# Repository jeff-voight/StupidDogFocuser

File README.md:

# StupidDogFocuser

## Open-source electronic telescope focuser

The StupidDogFocuser is a work-in-progress prototype electronic focuser. It shall eventually comply with ASCOM and INDI and should operate on Linux, Windows, or Mac.

## Goals

The goal of this project is to develop an electronic focuser that is compact, free of airwires, capable of being mounted to a variety of telescope focusers controllable via a PCB-mounted knob, serial commands, and INDI and ASCOM software. It should be inexpensive, easy to build at home, and only use components that are easy to acquire.

Ultimately, I want somebody to be able to have a neat, compact focuser for under $100 and their time and solder.

## Size and Shape

The PCB is a shield for an Arduino UNO R3. I hope to be able to etch and solder the board at home, but it should also be designed in such a way that one could order a commercially manufactured board. The KiCad design files will be included. The initial builds will be geared toward a commercial board house.

The board is approximately the same shape as the UNO. It receives the 12V power directly from the Arduino. That means that you need to plug the Arduino into a 12V 1A power supply. These are available where you bought the Arduino. We could get more torque and speed if we went with a higher voltage, but we don't really need more torque or speed.

On one end is an optional temperature/humidity sensor. During assembly, the legs of the package need to be bent so that the sensor can be layed flat extended out in space beyond the board. This, hopefully, keeps the sensor far enough away from the driver that it isn't affected and it provides a way to extend the sensor out of an enclosure to give it access to the outdoor air.

The board features a mounted rotary encoder for handheld use. In fact, if one were so inclined, one wouldn't necessarily need to enclose this focuser. One could very easily just put the hat on the arduino, wire up the motor, plug it into 12V, and hold the thing bare and be up and running without an enclosure.

Heck, you could hot glue the whole thing right on your observatory wall or telescope mount and be fine. Maybe clean the spiders out from time to time. I mean, don't let it rain on it, but you weren't going to let it rain on your telescopes, right? 

The encoder has 30 detents, but something I didn't realize at first was that the encoder counts two steps per detent. At first I fretted about this, but at 5400 steps per rotation on a 27:1 geared stepper running at half-stepping (for torque and performance), two steps per detent seemed like an acceptable trade-off. If you're running a 200 step stepper, you *should* still be okay on a refractor or reflector. I can't say for an SCT.

## Enclosure
Included is a 3d-printable set of STL files that worked for me. It even has a knob.

I printed mine in glow-in-the-dark. It has never helped.

I hope to find a more professional enclosure, but I'm not actively looking.

Along with the enclosure, I haven't included the panel-mount electrical connector because I haven't found a 6 pin connector that I like.

I'm currently using a 4-pin aircraft something something. If you have a 6-pin (2 pins for the limit switch) connector that you love and you 
can find it on digikey, feel free to fork the code and submit a pull request.

## Assembly
The PCB is designed to use the same resistors and the same capacitors throughout. You can't go wrong. Just solder the resistors in wherever you see a resistor footprint and the same for the capacitors.

The DHT11 or DHT22 needs to be layed flat if you want it to stick out of an enclosure. This bend needs to be done before soldering.

The motor screw terminals should probably face in the same direction as the wires are going to go. There should be enough space to flip it around.

The Schmidtt Trigger footprint includes a dot and a little slanty line to indicate the dotted end of the chip. Make sure you get the orientation correct.

Likewise, the DRV8825 footprint includes a white rectangle on the same end that the chip of the DRV8825 daughterboard has. Make sure those line up, too.

The DRV8825 *ABSOLUTELY* needs the heatsink that comes with it. Make sure you put that thing on. It didn't take me but a few minutes to roast one of mine during development because I was being lazy.

The DRV8825 *ABSOLUTELY* needs to be adjusted before plugging in your first stepper. The steppers that I've been getting have been running best at about .8A per coil. But, the motor gets HOT.

### DIY disclaimer
I'm not opposed to through-hole parts, but I personally find drilling boards to be the most difficult part of home manufacture of PCB, I'd rather keep the drill-file to a minimum. Consider that you're going to be drilling all of the Arduino header pins and all of the component pins. It's probably safest to order the boards from a board house. However, if you only drill out the holes you need, you can save a whole bunch of the arduino pin holes. You technically only need one ground pin. Make sure you carry the 12V and 5V pins through.

The KiCad PCBs will be done for _my_ convenience for now. That means tiny traces and silkscreen that I wouldn't dare do at home and drill holes galor and if I feel like throwing in a via collection that carries signals and looks like a moose, that's my prerogative.

I mean, I probably won't, but just in case I do.

## Calibration and limit switches

Another goal is a limit switch and a reset routine. Upon hard reset (if there is such a thing), on power-up, it would store it's current position, rack the focuser IN until it touched the limit switch, reset everything such the limit switch is the low limit and the original position gets restored to it's whatever position it was before. I've included the pins for the limit switch, but I haven't yet worked out a homing routine. When it happens, you'll probably need to build a focuser for each telescope you want to drive because the results of the homing and length of focus will get stored in EEPROM.

One way or another, I feel like I need some type of security such that my cameras never fall to the floor or I end up stripping a gear on the focuser.

That said, it hasn't been a problem _yet_.

## Power-Off Conditions

For the time being, all is lost on reset/power-off. We start the focuser in the 20,000s. That should be enough to give a couple of inward turns of a knob.

A limit switch would solve this.

# As it is

As it is, we communicate at 115,200 baud. We depend on AccelStepper and a high performance encoder library, so I don't want to slow either of those down with slow serial performance. Our signal is only going a few feet, and unless you've got outrageous amounts of noise, 115,200 will be fine.

# Commands

Serial commands are as follows:

| Command | Description | Response        | Defaults | Comments |
| ---     | ---         | ---             | ---      | --- |
| \<HA>	  | Halt        | HA!             | N/A      | as quickly as possible |
| \<GE> 	  | Is enabled? | [T\|F]!          | True     | Motor Driver |
| \<GR>     | Is reversed?| [T\|F]!          | False    | Motor direction |
| \<GM>     | Microsteps  | [1-32]!         | _(1/)_1  | Denominator (not yet functional) | 
| \<GH>     | High limit  | MAXINT! | 108000    | Distance from initial |
| \<GL>     | Low limit   | [0! | 0  | 32 bit int |
| \<GS>     | Speed       | [0-255]!      | 255     | Stepper motor dependent |
| \<GT>     | Temperature | %f.2!             | N/A      | DHT11/22 precision  |
| \<GP>     | Position    | 0-MAXINT! | 0        | Previous focus position |
| \<IM>     | Moving?     | [T\|F]!          | F        | True during movement |
| \<AM%d>   | Absolute Move | %d! (target) | N/A      | Target position|
| \<RM%d>   | Relative Move | %d! (target) | N/A      | Target position |
| \<RD[T\|F]>     | Reverse Motor | [T\|F]!       | N/A      | Response is new is reversed |
| \<SY%d>   | Sync Motor | %d! (same as param) | N/A  | |
| \<EN>     | Enable motor | EN!          | N/A| ||
| \<DI>     | Disable motor| DI!          | N/A | |
| \<SM[1-32]> | Set Microstepping 1/1 - 1/32 | %u! | 1 | New microstep mode (not yet functional)|
| \<SP%u>   | Set Speed 200-4000 | %d! | New speed | 1000 | Measure your motor to determine |
| \<SH%d>   | Set high limit | %d! | 32767 | Response is new high |
| \<SL%d>   | Set low limit  | %d! | -32768 | Response is new low limit |

Any error will trigger ERROR(optional message)#

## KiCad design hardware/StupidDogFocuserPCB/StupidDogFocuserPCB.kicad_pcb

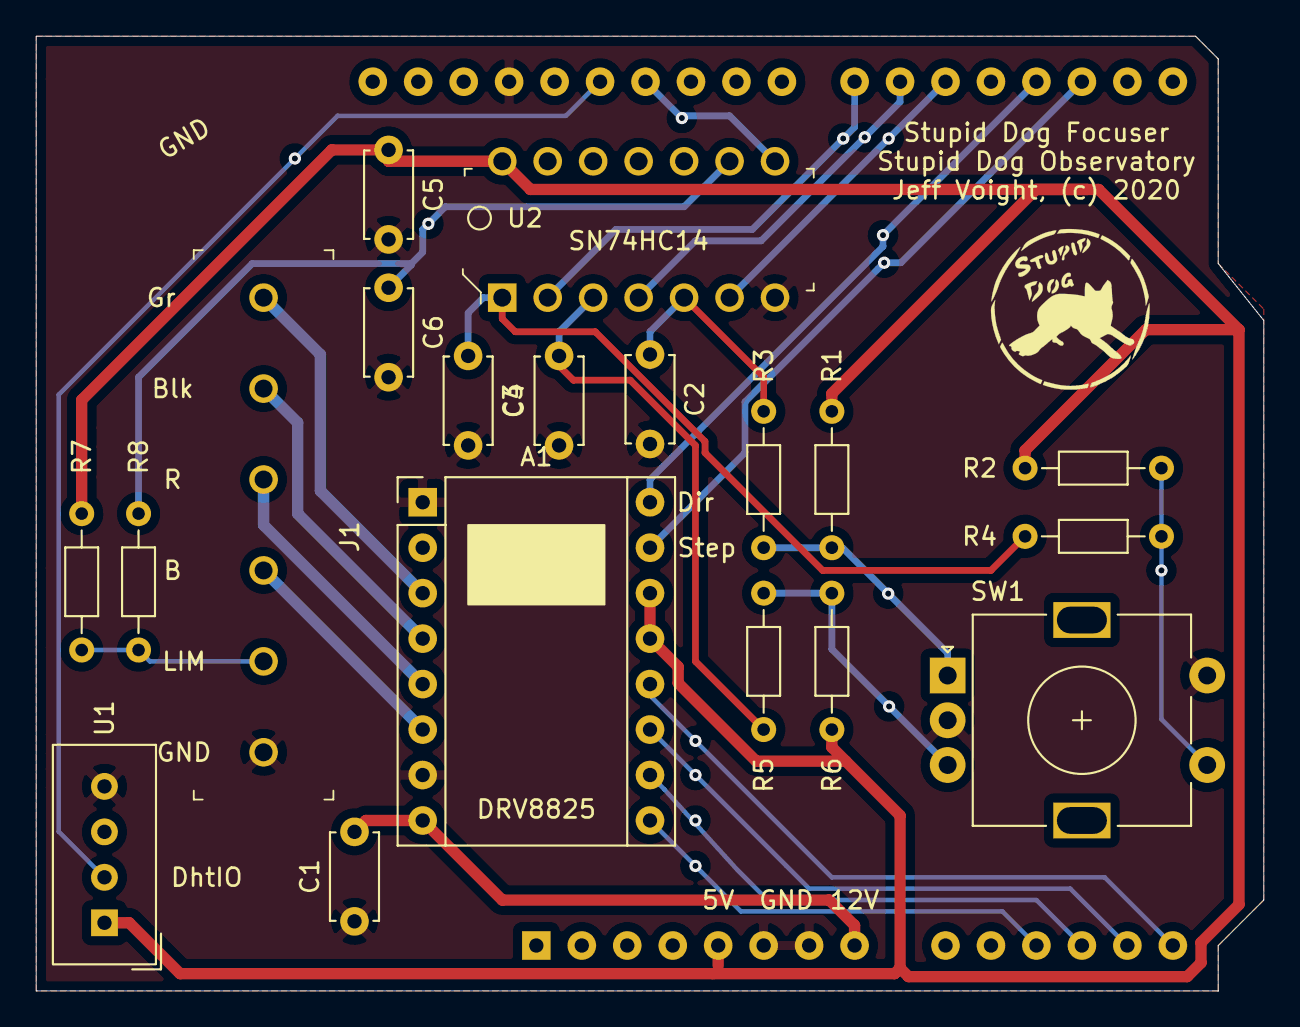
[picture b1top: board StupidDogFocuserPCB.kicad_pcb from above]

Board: 2 copper layers, 68.6 x 53.3 mm, 21 parts (1 on the bottom side), 26 nets.

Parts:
A1: Pololu_Breakout_DRV8825; Pololu_Breakout-16_15.2x20.3mm
A2: Arduino_UNO_R3
C1, C2, C3, C4, C5, C6: 4.7uF; C_Disc_D4.7mm_W2.5mm_P5.00mm
G1: LOGO; Stupid_dog_logo_small
J1: OSTTC062162; Term_Block_1x6_P5.08mm
R1, R2, R3, R4, R5, R6, R7, R8: 1k; R_Axial_DIN0204_L3.6mm_D1.6mm_P7.62mm_Horizontal
SW1: Rotary_Encoder_Switch; RotaryEncoder_Alps_EC11E-Switch_Vertical_H20mm
U1: DHT11; Aosong_DHT11_5.5x12.0_P2.54mm
U2: SN74HC14N; DIP-14_W3mm

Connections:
BL: A1.6, J1.4
BLK: A1.4, J1.2
DHT: A2.27, U1.2
Dir: A1.16, A2.18
ENCA: A2.20, U2.6
ENCA_A: C2.1, R3.1, U2.5
ENCB: A2.21, U2.4
ENCB_A: C4.2, R5.2, U2.3
G: A1.3, J1.1
GND: A1.1, A1.7, A2.6, A2.7, A2.29, C1.1, C2.2, C3.2, C4.1, C5.2, C6.2, J1.6, SW1.C, SW1.S2, U1.4, U2.7
LIM: A2.26, U2.8
LIM_A: C6.1, R8.1, U2.9
LIM_SW: J1.5, R7.2, R8.2
M0: A1.10, A2.12
M1: A1.11, A2.13
M2: A1.12, A2.14
unnamed: R1.2, R3.2, SW1.A
unnamed: R2.2, R4.2, SW1.S1
unnamed: R5.1, R6.1, SW1.B
R: A1.5, J1.3
SW: A2.22, U2.2
SW_A: C3.1, R4.1, U2.1
Step: A1.15, A2.17
VCC: A1.13, A1.14, A2.5, C5.1, R1.1, R2.1, R6.2, R7.1, U1.1, U2.14
VDD: A1.8, A2.8, C1.2
~Enable: A1.9, A2.11

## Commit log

2019-06-02 Initial project creation.
2019-06-02 added logo
2020-02-16 Init (#8)
    * init dirs
    * more directories
2020-02-16 Init (#9)
    * init dirs
    * more directories
    * Sketch compiles and responds to limitted commands.
    * typo
    * redundant variables
    * Strip debug
2020-02-16 enable (#10)
2020-02-17 brackets (#11)
2020-02-17 kicad drawing. Single layer. I don't like it. (#12)
2020-02-17 Remap/pins (#14)
    * Remapped kicad pins. Still need to map firmware.
    * no connections added to unused pins.
    * moved dht pin.
    * moved pins in sketch. Added optimize interrupts flag. Changed error messages.
2020-02-17 Initial check-in of the INDI Stupid Dog Focuser. (#15)
2020-02-17 Initial check-in of the INDI Stupid Dog Focuser.
2020-02-19 gitignore
2020-02-19 Indi/clearout (#16)
    * gitignore
    * Deleted Backlash, speed controls, and switches.
    * Serial Connection. Updated sendCommand and readResponse to handle tty.
    * erant trace removed
    * thicker traces
    * gitignore
2020-02-22 Readme (#17)
    * readme contents
    * readme contents
    * readme contents
    * readme contents
    * Serial commands defined in README.md and .h
    * README
2020-02-24 Hardware/cleanup (#22)
    * added m1 and m2
    * gerbers
2020-03-01 Command refactor (#23)
    * checkpoint
    * got the indi driver working sort of
    * serial working for now.
    * checkpoint
    * got the indi driver working sort of
    * serial working for now.
2020-03-07 Hardware/bugs (#26)
    * ASCOM6 Template
    * ASCOM commands ported in from firmware
    * remove readme.htm. Will replace with Readme.md when I get around to it.
    * Updated schematic. Added limit switch. Moved encoder to the right and the stepper to the left. Adjusted resistor and capacitor sizes. Added screw terminals. Moved DHT11 to where it can bend out.
    * thicker traces for the home gamer. Cleanup bends. Moved test points around.
    * regenerate gerbers
2020-03-07 Firmware/pinupdate (#27)
    * iml file ignored
    * Change pin definitions. Did some light housekeeping.
2020-03-12 Feature/pcbready (#30)
    * cache update kicad?
    * added temperature read back in
    * minor tweaks to the code now that the PCB works.
    * update indi driver to reflect changes. Remove microstep.
    * speed read
2020-03-13 Feature/bompcbpads (#31)
    * bill of materials
    * added ground clip pad. Updated capacitor sizes. Regenerated gerbers.
2020-03-13 updated commands (#32)
2020-03-13 oops (#33)
2020-03-13 Feature/ascom driver (#34)
    * ASCOM6 Template
    * ASCOM commands ported in from firmware
    * remove readme.htm. Will replace with Readme.md when I get around to it.
2020-03-16 larger holes for screw terminals. Ground pad for testing.
2020-03-17 Updating Readme
2020-03-26 Feature/case st ls (#35)
    * larger holes for screw terminals. Ground pad for testing.
    * Updating Readme

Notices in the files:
hardware/StupidDogFocuserPCB/StupidDogFocuserPCB.kicad_pcb:
Copyright, 2020
Jeff Voight, (c) 2020
